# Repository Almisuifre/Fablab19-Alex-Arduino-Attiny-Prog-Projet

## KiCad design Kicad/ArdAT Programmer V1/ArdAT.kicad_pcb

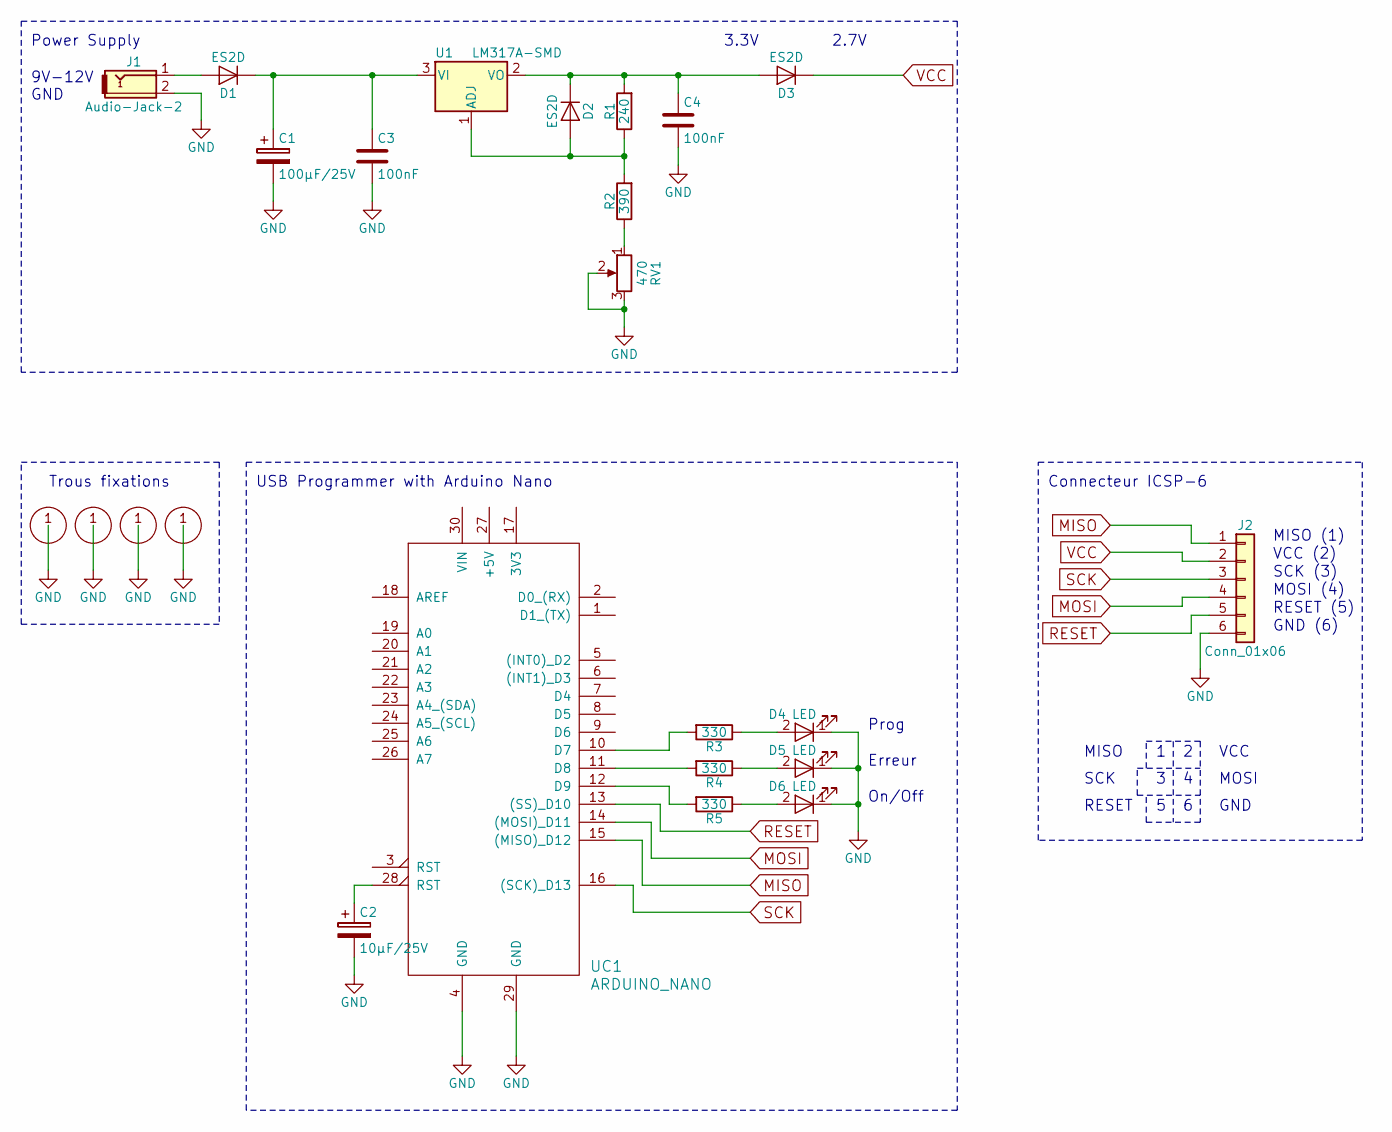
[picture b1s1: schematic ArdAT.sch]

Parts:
C1: 100µF/25V; CP_Elec_6.3x7.7
C2: 10µF/25V; CP_Elec_5x5.3
C3, C4: 100nF; C_0805_HandSoldering
D1, D2, D3: ES2D; D0-214
D4, D5, D6: LED; LED_D3.0mm
H1, H2, H3, H4: M3-Hole
J1: Audio-Jack-2; Connecteur-Embase-Debrochable-2_Voies
J2: Conn_01x06; 2x3-Pin-Connecteur
R1: 240; R_0805_HandSoldering
R2: 390; R_0805_HandSoldering
R3, R4, R5: 330; R_0805_HandSoldering
RV1: 470; Potentiometer_Trimmer_Bourns_3296X
U1: LM317A-SMD; T0-252-SMD
UC1: ARDUINO_NANO

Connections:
GND: C1.2, C2.2, C3.2, C4.2, D4.1 (K), D5.1 (K), D6.1 (K), H1.1, H2.1, H3.1, H4.1, J1.2, J2.6, RV1.2, RV1.3, UC1.4 (GND), UC1.29 (GND)
MISO: J2.1, UC1.15 ((MISO)_D12)
MOSI: J2.4, UC1.14 ((MOSI)_D11)
unnamed: C1.1, C3.1, D1.1 (K), U1.3 (VI)
unnamed: C2.1, UC1.28 (RST)
unnamed: C4.1, D2.1 (K), D3.2 (A), R1.2, U1.2 (VO)
unnamed: D1.2 (A), J1.1
unnamed: D2.2 (A), R1.1, R2.2, U1.1 (ADJ)
unnamed: D4.2 (A), R3.1
unnamed: D5.2 (A), R4.1
unnamed: D6.2 (A), R5.1
unnamed: R2.1, RV1.1
unnamed: R3.2, UC1.10 (D7)
unnamed: R4.2, UC1.11 (D8)
unnamed: R5.2, UC1.12 (D9)
RESET: J2.5, UC1.13 ((SS)_D10)
SCK: J2.3, UC1.16 ((SCK)_D13)
VCC: D3.1 (K), J2.2

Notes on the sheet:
MISO (1)
SCK (3)
MOSI (4)
RESET (5)
GND (6)
VCC (2)
Prog
Erreur
On/Off
Trous fixations
Power Supply
9V-12V GND
USB Programmer with Arduino Nano
Connecteur ICSP-6
MISO
MOSI
SCK
GND
VCC
RESET
3.3V
2.7V

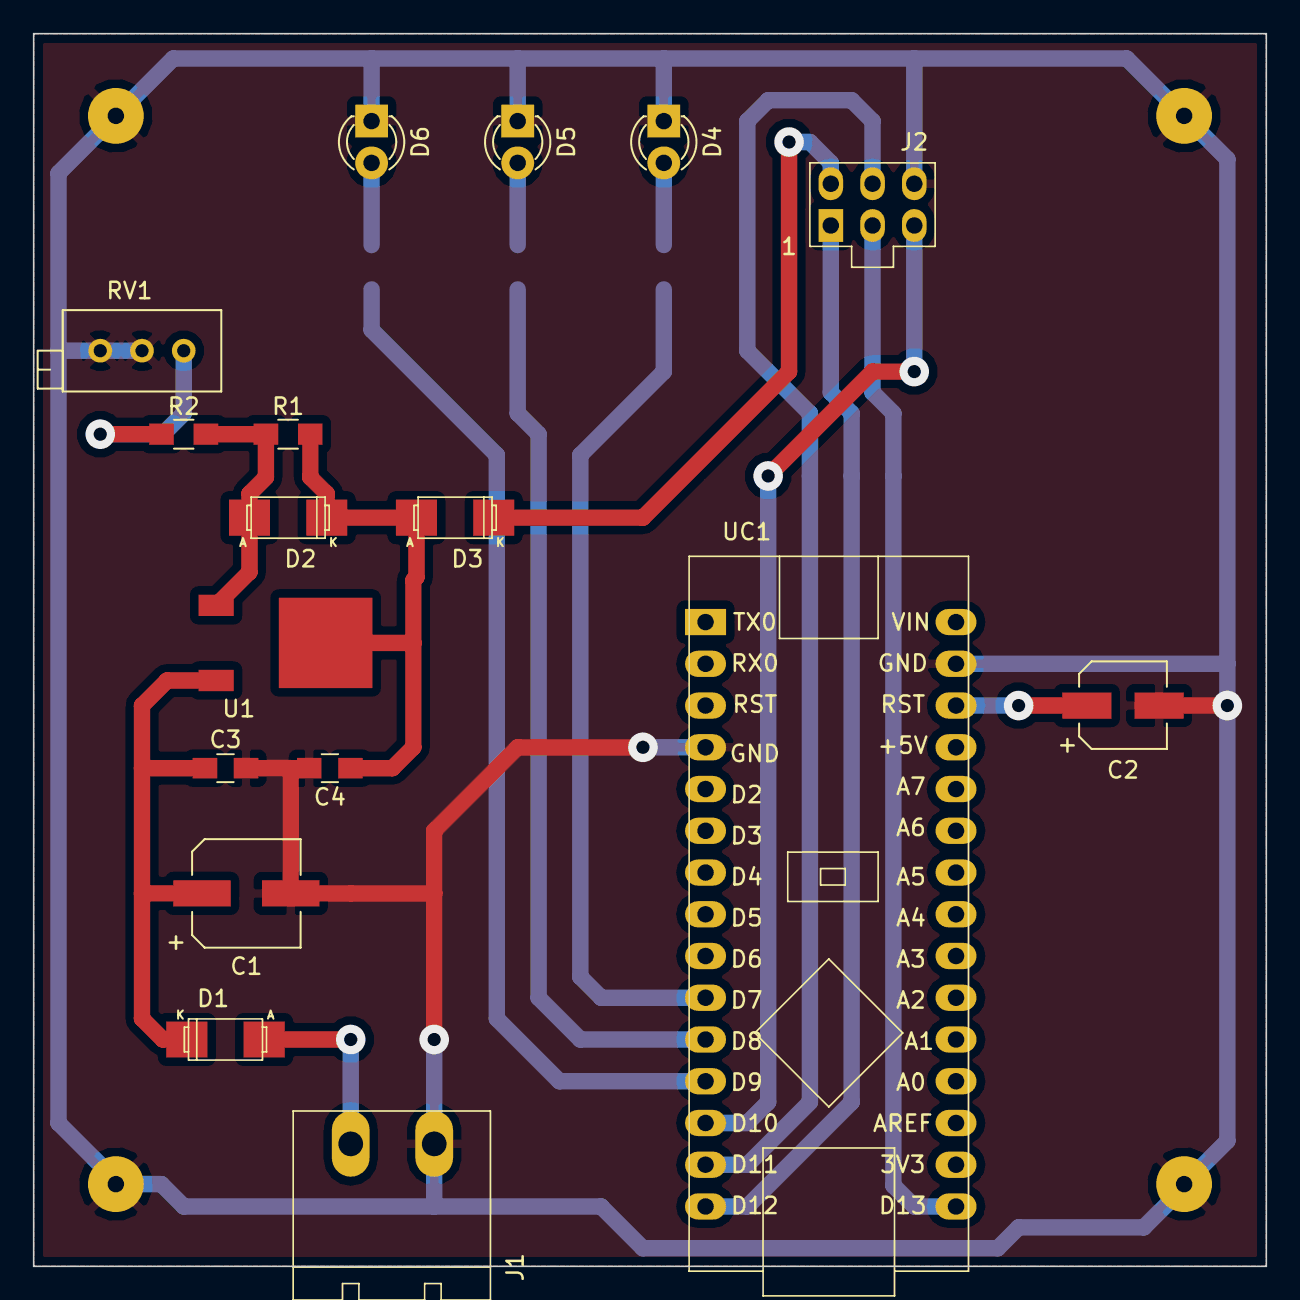
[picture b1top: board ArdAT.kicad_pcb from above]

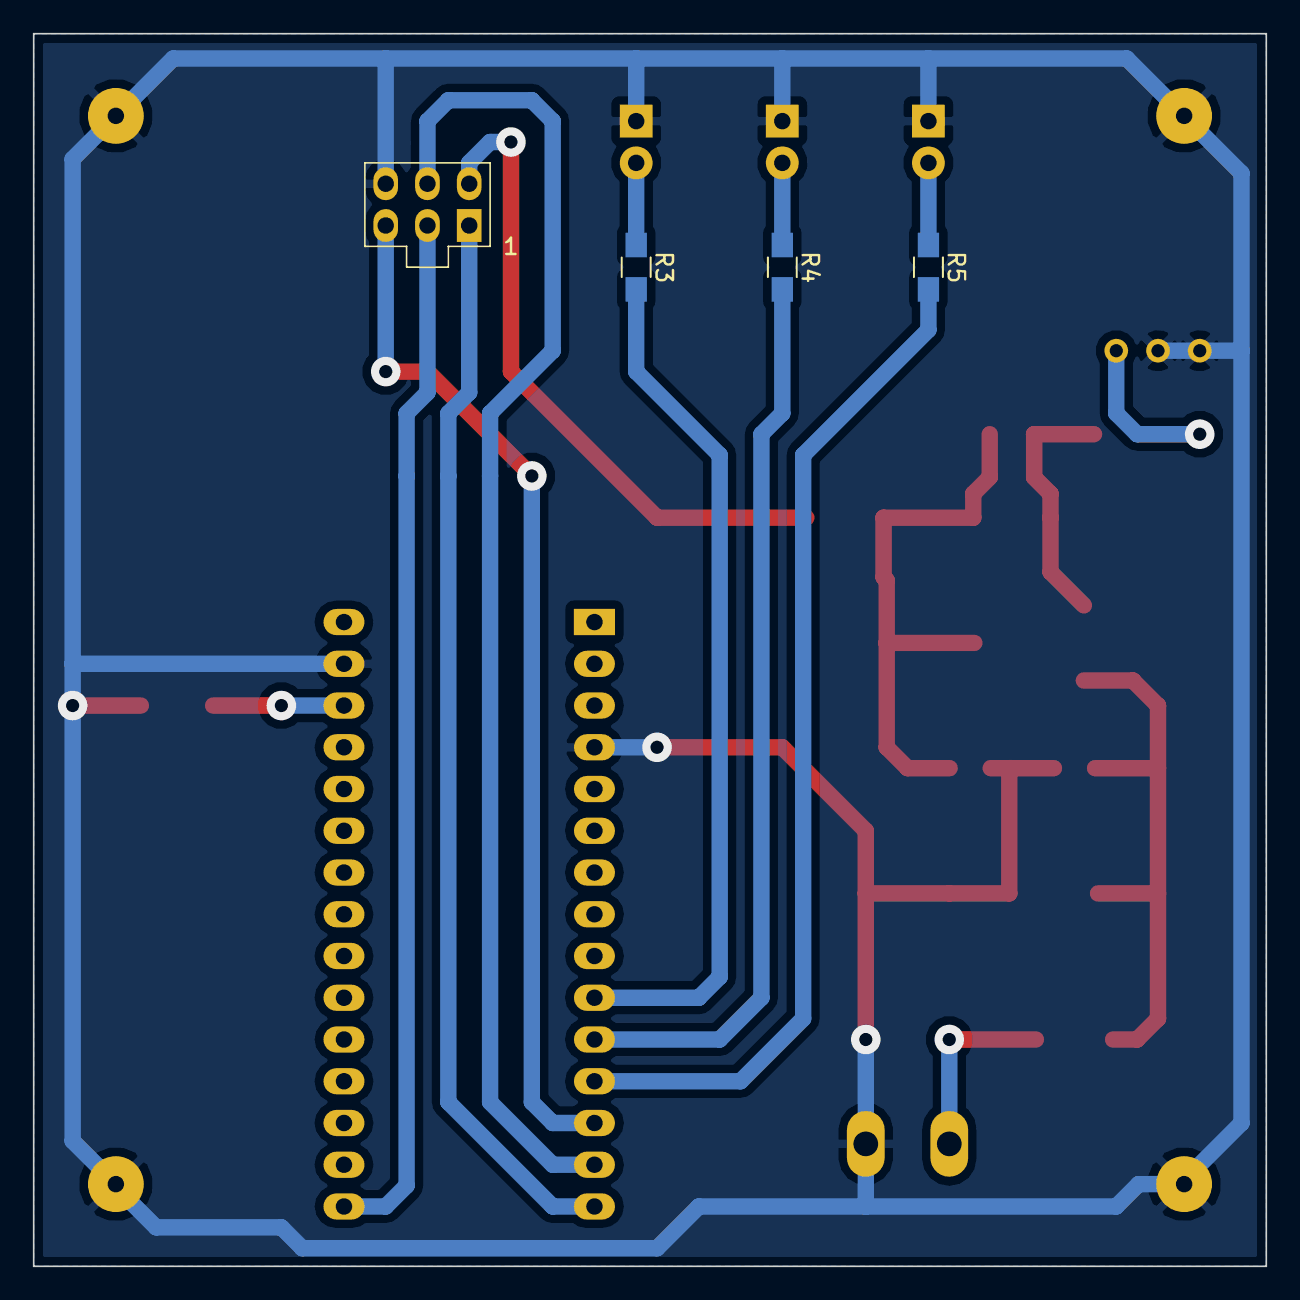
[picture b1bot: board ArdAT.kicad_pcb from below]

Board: 2 copper layers, 75.0 x 75.0 mm, 24 parts (3 on the bottom side), 18 nets.

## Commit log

2018-04-18 Create project
    Create project
    Add schematic project
2018-04-20 Update
    Update 3.3V
2018-04-22 Create PCB
    Create PCB
2018-04-23 Update
    Update
2018-05-02 Update
    Add box
